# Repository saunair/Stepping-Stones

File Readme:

The code is launched in the master PC by the following commands in different terminals
roslaunch morpheus_skates stepping_stones.launch
rosrun morpheus_skates take_user_input.py
rosrun morpheus_skates shoe_size_input.py

Calibration routine:
roslaunch morpheus_skates calibration_arduino.py

The folder structure is created in a way that all the components are separate from each other
Arduino contains all the object oriented code that runs in each skate
CATKIN workspace contains all the ROS code 
Matlab contains the ROSBAGs, ROSBAG parsing scripts and some simulation files
Mechanical/CAD has all the CAD files of the skates 
Electrical Contains the PCB schematic and layouts used for power distribution and sensing

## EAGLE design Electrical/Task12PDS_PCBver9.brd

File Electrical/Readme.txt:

Schematic and Layout Designs for Power distribution and sensing suite PCB.

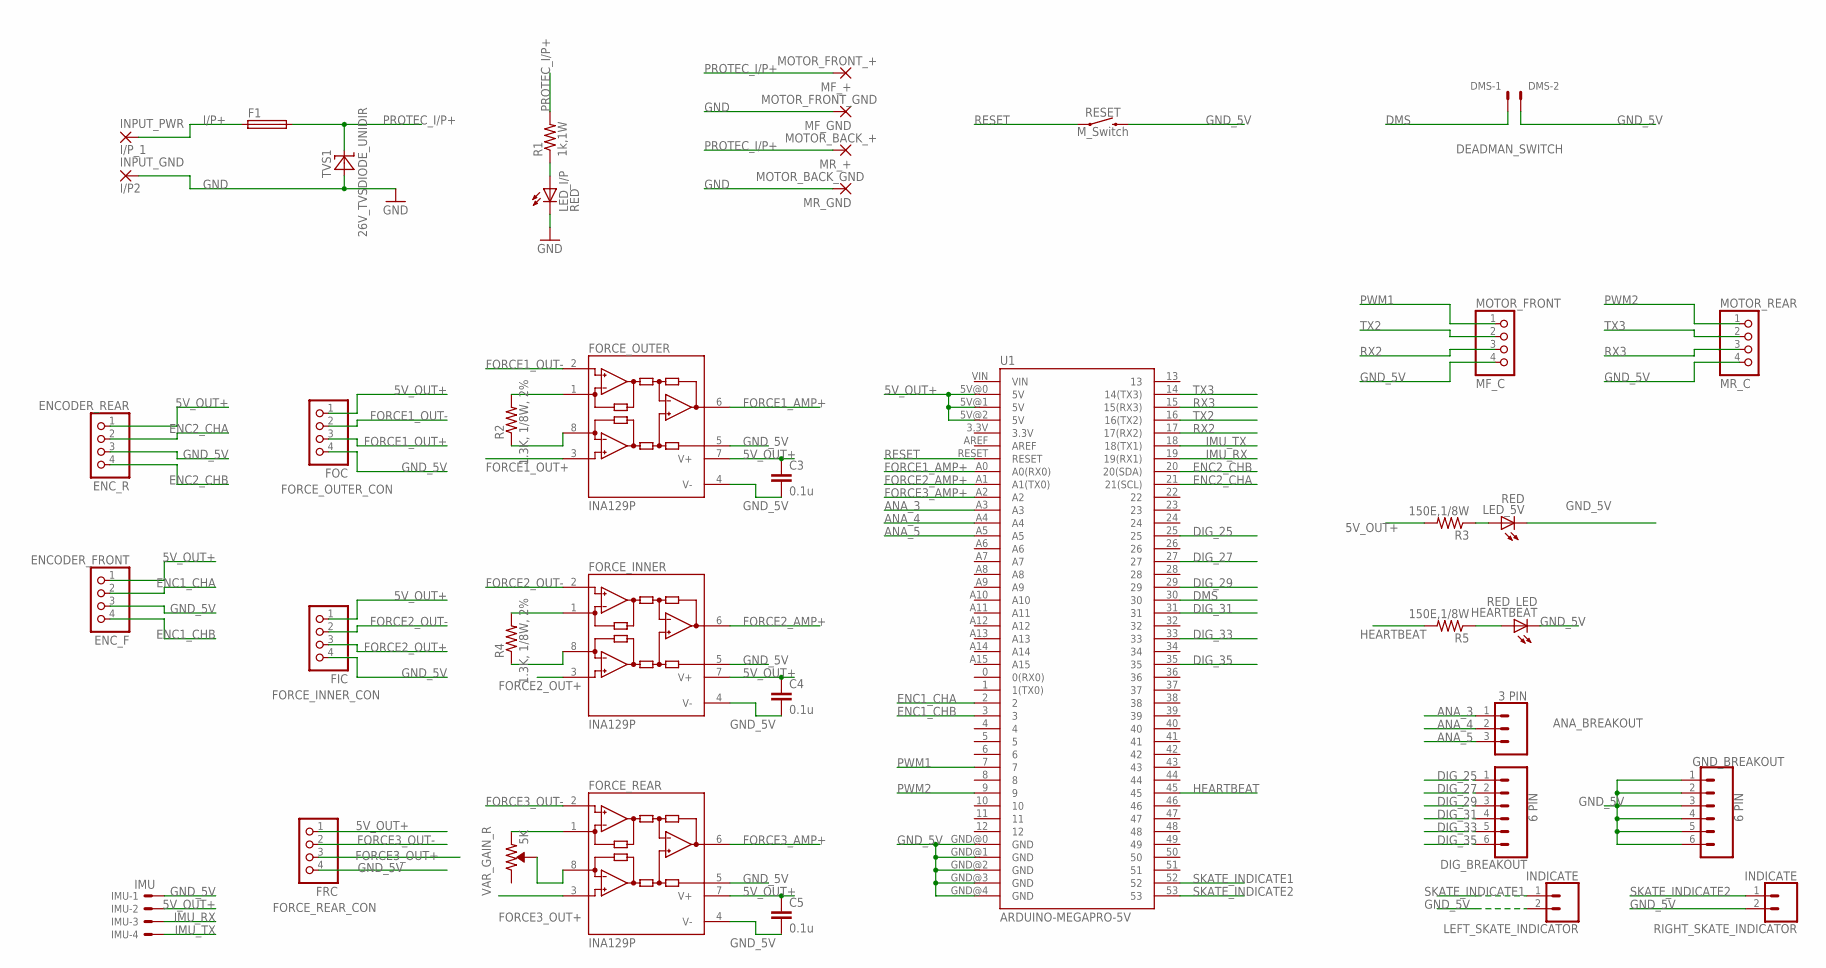
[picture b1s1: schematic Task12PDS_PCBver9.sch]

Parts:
ANA_BREAKOUT: 3 PIN; 1X03
C3, C4, C5: 0.1u; C1206
DIG_BREAKOUT: 6 PIN; 1X06
DMS: DEADMAN_SWITCH; 22-23-2021
ENCODER_FRONT: ENC_F; 1X04/90
ENCODER_REAR: ENC_R; 1X04/90
F1: FASTBLOW_FUSE_10A; TE5
FORCE_INNER: INA129P; DIL08
FORCE_INNER_CON: FIC; 1X04/90
FORCE_OUTER: INA129P; DIL08
FORCE_OUTER_CON: FOC; 1X04/90
FORCE_REAR: INA129P; DIL08
FORCE_REAR_CON: FRC; 1X04/90
GND_BREAKOUT: 6 PIN; 1X06
HEARTBEAT: RED_LED; 1206
IMU: IMU; 22-23-2041
INPUT_GND: I/P2; 3,81/1,1
INPUT_PWR: I/P_1; 3,81/1,1
LED_5V: RED; 1206
LED_I/P: RED; 1206
LEFT_SKATE_INDICATOR: INDICATE; 1X02
MF_+: MOTOR_FRONT_+; 3,81/1,1
MF_GND: MOTOR_FRONT_GND; 3,81/1,1
MOTOR_FRONT: MF_C; 1X04/90
MOTOR_REAR: MR_C; 1X04/90
MR_+: MOTOR_BACK_+; 3,81/1,1
MR_GND: MOTOR_BACK_GND; 3,81/1,1
R1: 1k,1W; M1206
R2, R4: 1.3K, 1/8W, 2%; M1206
R3, R5: 150E,1/8W; M1206
RESET: M_Switch; TACTILE_SWITCH_PTH_6.0MM
RIGHT_SKATE_INDICATOR: INDICATE; 1X02
TVS1: 26V_TVSDIODE_UNIDIR; DO214AC
U1: ARDUINO-MEGAPRO-5V; ARDUINO_MEGA-PRO-5V
VAR_GAIN_R: 5K; TRIMPOT-PTH-3386U

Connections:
5V_OUT+: C3.1, C4.1, C5.1, ENCODER_FRONT.1, ENCODER_REAR.1, FORCE_INNER.7 (V+), FORCE_INNER_CON.1, FORCE_OUTER.7 (V+), FORCE_OUTER_CON.1, FORCE_REAR.7 (V+), FORCE_REAR_CON.1, IMU.2, R3.2, U1.5V@0 (5V), U1.5V@1 (5V), U1.5V@2 (5V)
ANA_3: ANA_BREAKOUT.1, U1.A3
ANA_4: ANA_BREAKOUT.2, U1.A4
ANA_5: ANA_BREAKOUT.3, U1.A5
DIG_25: DIG_BREAKOUT.1, U1.25
DIG_27: DIG_BREAKOUT.2, U1.27
DIG_29: DIG_BREAKOUT.3, U1.29
DIG_31: DIG_BREAKOUT.4, U1.31
DIG_33: DIG_BREAKOUT.5, U1.33
DIG_35: DIG_BREAKOUT.6, U1.35
DMS: DMS.1, U1.30
ENC1_CHA: ENCODER_FRONT.2, U1.2
ENC1_CHB: ENCODER_FRONT.4, U1.3
ENC2_CHA: ENCODER_REAR.2, U1.21 (21(SCL))
ENC2_CHB: ENCODER_REAR.4, U1.20 (20(SDA))
FORCE1_AMP+: FORCE_OUTER.6 (OUT), U1.A0 (A0(RX0))
FORCE1_OUT+: FORCE_OUTER.3 (+IN), FORCE_OUTER_CON.3
FORCE1_OUT-: FORCE_OUTER.2 (-IN), FORCE_OUTER_CON.2
FORCE2_AMP+: FORCE_INNER.6 (OUT), U1.A1 (A1(TX0))
FORCE2_OUT+: FORCE_INNER.3 (+IN), FORCE_INNER_CON.3
FORCE2_OUT-: FORCE_INNER.2 (-IN), FORCE_INNER_CON.2
FORCE3_AMP+: FORCE_REAR.6 (OUT), U1.A2
FORCE3_OUT+: FORCE_REAR.3 (+IN), FORCE_REAR_CON.3
FORCE3_OUT-: FORCE_REAR.2 (-IN), FORCE_REAR_CON.2
GND: INPUT_GND.1, LED_I/P.C, MF_GND.1, MR_GND.1, TVS1.A
GND_5V: C3.2, C4.2, C5.2, DMS.2, ENCODER_FRONT.3, ENCODER_REAR.3, FORCE_INNER.4 (V-), FORCE_INNER.5 (REF), FORCE_INNER_CON.4, FORCE_OUTER.4 (V-), FORCE_OUTER.5 (REF), FORCE_OUTER_CON.4, FORCE_REAR.4 (V-), FORCE_REAR.5 (REF), FORCE_REAR_CON.4, GND_BREAKOUT.1, GND_BREAKOUT.2, GND_BREAKOUT.3, GND_BREAKOUT.4, GND_BREAKOUT.5, GND_BREAKOUT.6, HEARTBEAT.C, IMU.1, LED_5V.C, LEFT_SKATE_INDICATOR.2, MOTOR_FRONT.4, MOTOR_REAR.4, RESET.3 (2), RIGHT_SKATE_INDICATOR.2, U1.GND@0 (GND), U1.GND@1 (GND), U1.GND@2 (GND), U1.GND@3 (GND), U1.GND@4 (GND)
HEARTBEAT: R5.2, U1.45
I/P+: F1.1, INPUT_PWR.1
IMU_RX: IMU.3, U1.19 (19(RX1))
IMU_TX: IMU.4, U1.18 (18(TX1))
unnamed: HEARTBEAT.A, R5.1
unnamed: FORCE_OUTER.1 (RG), R2.2
unnamed: LED_I/P.A, R1.1
unnamed: FORCE_OUTER.8 (RG), R2.1
unnamed: LED_5V.A, R3.1
unnamed: FORCE_INNER.1 (RG), R4.2
unnamed: FORCE_INNER.8 (RG), R4.1
unnamed: FORCE_REAR.1 (RG), VAR_GAIN_R.1 (CCW)
unnamed: FORCE_REAR.8 (RG), VAR_GAIN_R.2 (WIPER)
PROTEC_I/P+: F1.2, MF_+.1, MR_+.1, R1.2, TVS1.C
PWM1: MOTOR_FRONT.1, U1.7
PWM2: MOTOR_REAR.1, U1.9
RESET: RESET.1, U1.RESET
RX2: MOTOR_FRONT.3, U1.17 (17(RX2))
RX3: MOTOR_REAR.3, U1.15 (15(RX3))
SKATE_INDICATE1: LEFT_SKATE_INDICATOR.1, U1.52
SKATE_INDICATE2: RIGHT_SKATE_INDICATOR.1, U1.53
TX2: MOTOR_FRONT.2, U1.16 (16(TX2))
TX3: MOTOR_REAR.2, U1.14 (14(TX3))

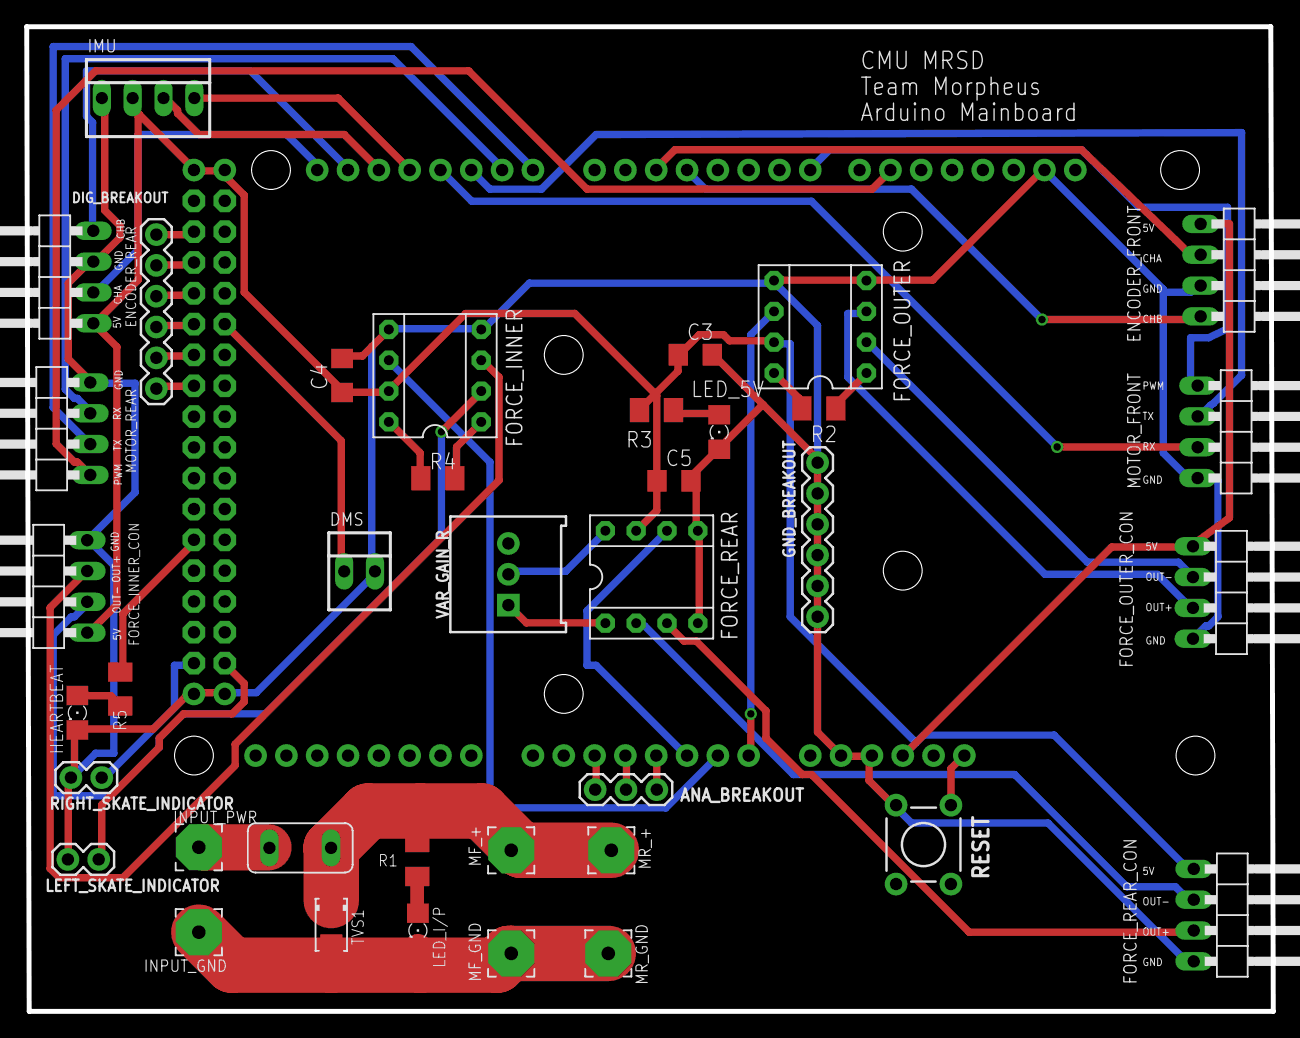
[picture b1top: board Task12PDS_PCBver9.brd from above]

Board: 2 copper layers, 102.7 x 81.2 mm, 40 parts (0 on the bottom side), 49 nets.

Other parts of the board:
DRILEGEND: DRILEGEND

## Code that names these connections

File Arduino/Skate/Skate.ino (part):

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#define FRC_INNER_CH 0
#define FRC_REAR_CH 2

#define ENC1_CHA_PIN 2
#define ENC1_CHB_PIN 3

#define ENC2_CHA_PIN 21
#define ENC2_CHB_PIN 20

#define DEAD_MAN_SW_PIN 30
#define HEARTBEAT_PIN 45

#define CTRL_PERIOD_MS 10.0
#define SAMP_PERIOD_MS 2.0
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
Force forceSensors(FRC_OUTER_CH,FRC_INNER_CH,FRC_REAR_CH);

Drive frontDrive(ENC1_CHA_PIN,ENC1_CHB_PIN,&Serial2); 
Control frontControl(posnGainsFront,velGainsFront,CTRL_PERIOD_MS);

Drive rearDrive(ENC2_CHA_PIN,ENC2_CHB_PIN,&Serial3);
Control rearControl(posnGainsRear,velGainsRear,CTRL_PERIOD_MS);

UM imu;
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  ADMUX  =  bit (REFS0) | (FRC_OUTER_CH & 0x07);    // AVcc and select input port

  //Set Up Front Skate
  attachInterrupt(digitalPinToInterrupt(ENC1_CHA_PIN), doEncoderFrontChA, CHANGE);
  attachInterrupt(digitalPinToInterrupt(ENC1_CHB_PIN), doEncoderFrontChB, CHANGE);
  frontDrive.initializeDrive();
  frontControl.setInvertFlag(leftSkate == true);

  //Set Up Rear Skate
  attachInterrupt(digitalPinToInterrupt(ENC2_CHA_PIN), doEncoderRearChA, CHANGE);
  attachInterrupt(digitalPinToInterrupt(ENC2_CHB_PIN), doEncoderRearChB, CHANGE);
  rearDrive.initializeDrive();
  rearControl.setInvertFlag(leftSkate == true);

  pinMode(DEAD_MAN_SW_PIN, INPUT_PULLUP);
  pinMode(HEARTBEAT_PIN, OUTPUT);

  Serial1.begin(115200);
  Serial1.write(allRequests,21);
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    frontDrive.resetTimeout();
    rearDrive.resetTimeout();

    digitalWrite(HEARTBEAT_PIN,!digitalRead(HEARTBEAT_PIN));
  }
}

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
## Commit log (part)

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2016-11-25 first arduino commit
2016-11-26 "arduino"
2016-11-26 "mechanical"
2016-11-29 "updated arduino codes"
2016-11-29 "new ros codes"
2016-11-30 delayed working code
2016-11-30 at night
2016-11-30 with user input node
2016-11-30 just for arduino
2016-12-01 with new integration code for arduino
2016-12-01 velocity PID working
2016-12-01 Create velocity_control_left
2016-12-01 not working, but compiling arduino
2016-12-07 Add files via upload
    Uploading latest low_level_controller with working position and velocity control. Copy the Servo.h to your local Servo library folder to enable higher speed PWM outputs.
2016-12-07 Create low_level_controller
2016-12-08 with ros integration working and tested
2016-12-08 ros code 7th dec
2016-12-08 with working ros code and skates 11:57pm 7th december
2017-01-26 Updated ROS Arduino code to correct encoder velocity calculation. - Requires testing
2017-01-27 new commit for calibration changes xX
2017-01-27 fixed a bug in the calibration routine
2017-01-30 partially working calibration code
2017-02-01 push for code transition
2017-02-01 brad's
2017-02-01 with the control integration
2017-02-05 removed build
2017-02-05 removed devel
2017-02-05 adding the latest openni launch
2017-02-05 adding the latest openni tracker
2017-02-05 adding the latest rosserial
2017-02-05 Madgwik
2017-02-05 openni_camera
2017-02-05 removing april tage
2017-02-05 Adding serial package
2017-02-05 removing openni-2 files
2017-02-05 removing mrsd packages
2017-02-06 Added serial_motor_commander which accepts a command -100 to +100, maps it to the appropriate pwm command, drives the speed controller, and returns the encoder value.
2017-02-08 heartbeat tetsed
2017-02-08 fixing git
2017-02-08 fixing_git
2017-02-08 fixing_git_rosserial
2017-02-10 removing the useless files
2017-02-12 with faults and kinect centering
2017-02-12 test
2017-02-12 separate faults for skates
2017-02-13 fixed a few offline bugs
2017-02-15 fixed issues
2017-02-15 added files
2017-02-17 Baselined on updated nomenclature PR9_Feb11 code. Starting to split code into libraries.
2017-02-18 untested code
2017-02-18 Created initial object-oriented Arduino software "Skate"
2017-02-18 Added initial keywords.txt for function highlighting, but updates required.
    Added updated mechanical drawing of the aux shaft.
2017-02-19 Now actually deleted install to align
2017-02-19 added mechanical preload code, not tested!
2017-02-20 Started debugging class-based Arduino code, syntax errors and such
2017-02-20 The new class-based code compiles! Ready for minor changes and functional testing/debugging.
2017-02-22 Initial debugging of class-based Arduino code. Position control works on Left Skate. Currently fighting with velocity control - pulsing behavior. Added numerous debugging outputs through ROS. Modifie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
2017-02-24 Completed initial debugging and development of object-based code. Controls still needs work but performs reasonably under load or at speeds of 200 or higher. Replaced moving average filters with trac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
2017-02-24 Changed controller gains to improve performance slightly
2017-02-24 Updated force sensing code after testing. Works for all three sensors.
2017-02-25 partially working calibration
2017-02-25 Started IMU integration coding.
2017-02-25 Updated Arduino code to reintegrate IMU - requires testing. IMU cpp and h moved into Skate folder to resolve compilation issue.
2017-02-25 Corrected IMU request for acceleration
2017-02-26 working normalization
2017-02-27 first compiled imu integrator
2017-02-28 calibration_values
2017-02-28 working calibration with preload
2017-02-28 Arduino code with working, lower rate IMU communication. Also wrote serial sniffer that allows an Arduino to forward and rebroadcast bidirectional serial communication allowing for monitoring from a 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
2017-02-28 Mounts for new PCB location over user's toe-box
2017-02-28 Committed change from this morning that supports more consistent publishing rate.
2017-03-04 trial normalization
2017-03-04 temporary normalization
2017-03-10 Intermediate commit wih 115,200 baud rate to resolve checksum errors. Trying to increase IMU and control loop rates.
2017-03-10 Achieved best balance of rates and capabilities. Control: 100Hz, IMU: 20Hz, Force: 500Hz
2017-03-10 Updated message with new elements including debug entries. Modified launch partially for baud rate.
2017-03-11 Corrected mistake in force reading - thanks Saurabh!
2017-03-11 Added in various minor changes related to skate side, baud, and publish rate.
2017-03-11 Added CAD files for Force Sensor Calibration Rig
2017-03-12 adding rest of the files
2017-03-12 Updates while calibrating. Pounds_display now works.
2017-03-13 Added previous scripts and rosbags. Need new rosbag to continue development.
2017-03-13 Added matlab script development bag. Pounds display message and related changes from yesterday. Cleanup changes from yesterday. Corrections to stepping_stones.py after testing.
2017-03-14 First pass at Matlab script and first rosbag conversion completed.
2017-03-14 With new topics in steping stones and preliminary IMU work
2017-03-15 Added rear terminal holder. Housekeeping of moving files to new spring folder.
2017-03-16 imu for debugging at home
2017-03-17 kou changed the channel numbers
2017-03-19 Created DriveCharacterization sketch to perform open loop motor testing with the VESC-X's. Initial code written, some debugging required for compilation.
2017-03-20 Committing older changes relating to imu integrator and normalization display
2017-03-20 Added VR script files for safe-keeping ahd hopefully to fix catkin_make
2017-03-20 Valid calibration values for all sensors with preload! Update Skate to pull-up digital inputs for skate indicators.
2017-03-20 Compilation errors resolved for the DriveCharacterization sketch. Functional testing still required.
2017-03-20 work for normalization
2017-03-20 fixes to normalization topic
2017-03-21 first bag files
2017-03-21 all bag files for static tests
2017-03-21 COM test data
2017-03-21 Updated DriveCharacterization from first level of functional debugging. Ready to test with VESC-X.
2017-03-21 Renamed scripts folder
2017-03-21 Partial updates to script for two added topics. Initial conversion of two rosbags out of interest.
2017-03-21 Mounts over user's toe-box for new PCB and the IMU
2017-03-22 Rosbag file parsing script
2017-03-22 Wrote script to combine normalized force readings from an experiment. Converted stance tests to mat and csv with script.
2017-03-22 Multiclass SVM for stance determination
2017-03-22 SVM with RBF and model
2017-03-22 Added script for combining com data and .mat combined file.
2017-03-22 Swapped front and rear encoder pin definitions to match new PCB.
2017-03-23 Migrated VESC-X code from DriveCharacterization to Skate. Updated controls code with preliminary feedforward and feedback elements/gains. Benchtop testing required.
2017-03-24 Initial debugging and tuning of VESC control.
2017-03-27 Control updates to handle skate directionality. Successfully tested all 4 motors with this code.
2017-03-27 progress with integrated message
2017-03-27 into test as well
2017-03-28 Updated Skate sketch for new feedback and command naming. Reenabled safety checks. Updated make list to make new essages. Updated subscribers to possible updated messages. Added foot keypoints to mes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
2017-03-28 adding publish rate message
2017-03-29 bug fixes with subscription
2017-03-29 zero point subtraction
2017-03-29 adding changes regarding timeout
2017-03-29 removing calibration enable
2017-03-29 yaml file
2017-03-29 with latest development in aggregated message
2017-03-29 Updates for better safety fault response.
2017-03-30 bag files and message node fix try
2017-03-30 Updates to parseRosbag for command and feedback message changes. Added integrated message but currently results in java memory error. Parsed multiple messages from last rosBag from plotting - noted e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
2017-03-31 Added tf listeners for other Kinect keypoints with print statements to test using stepping stones, success. Silenced repetitive messages for skate faults and timouts. Changed force normalization to u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
2017-04-02 Merged integrated message with stepping stones. Corrected issues in force normalization.
2017-04-02 Closed loop control testing
2017-04-03 Controls State Machine code
    Still in progress, have just laid out a basic skeleton so far; lots to do.
2017-04-03 Controls Skate Machine Skeleton
    Updated, mostly complete; need to fill in controls steps, weighting of the state transitions, discuss conditions for the same
2017-04-04 Open loop motor testing - potential rear left encoder problem and screw interference seized rear right motor in last test.
2017-04-04 Added Matlab ros msg gen stuff including duplication of workspace..sorry
2017-04-04 rosbag for open loop
2017-04-04 Arduino code with freewheeling. Matching rosbags.
2017-04-04 qupdated state machine
2017-04-05 Updated StateMachine works boi
2017-04-05 Ramp and gain updates to Arduino code. Control debug rosbags commited.
2017-04-05 Corrected state machine code
2017-04-05 Arduino code with tuned closed loop PI control. Control loop testing ros bags. Added time to total_message header.
2017-04-05 initial state machine progress
2017-04-07 progress
2017-04-07 state classifier
2017-04-07 Updated DriveCharacterization with revised encoder mapping for new PCB. Updated parseRosbag to parse total message. Completed parsing of first rosbag to .mat and .csv files.
2017-04-07 Added more parsed rosbags. Noticed an issue with the LeftCommand and RightCommand values staying at 0 - need to playback rosbags to determine if issue is in ros or matlab.
2017-04-08 Added conditions for clipping left, right, and total normalized forces. Increased preload threshold warning to 20% to reduce nuisance messages. Needs testing.
2017-04-08 Dummy NN code for velocity mapping
2017-04-08 vr code node
2017-04-09 Updates and bags from tonight's tests
2017-04-09 Parsed rosbags of tests from Saturday night. Finally committing V2 of bearing mount 3D printed part.
2017-04-12 progress with velocity mapper code
2017-04-12 updated with all feature additions
2017-04-12 Updated Arduino code with reduced Ki for tracking loop, new open loop gain, and unloaded Kp and Ki. Also included fix for state changes of brake and freewheeling. Updated stepping stones to remap lef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
2017-04-12 working velocity mapping code
2017-04-12 updated state machine with markov chain
2017-04-13 Initial version of wheel mount - need to correct hole locations and height.
2017-04-14 COM checks and additional code
2017-04-15 updated state machine code
2017-04-15 VR sender updates to node and launch. CL tuning with wheels for Koushik and Brad.
2017-04-15 Updated keystrokes to correct discretization logic.
2017-04-15 Added parsed rosbags from closed loop controls testing.
2017-04-15 state machine updates
2017-04-15 updates in feature vector addition
2017-04-15 State Machine changes
2017-04-15 additions for integration
2017-04-16 INtegrated state machine codes
2017-04-16 latest ROSBAGS model fitting
2017-04-16 Parsed rosbags from 4/15/2017 evening tests.
2017-04-17 rosbags with HDM
2017-04-17 debugs
2017-04-17 updated state machine
2017-04-18 Latest parsed rosbags. Initial comEstimator trial code. Updates to caster replacement CAD and STL files.
2017-04-22 kinect based velocity control
2017-04-22 Updated controller
2017-04-22 Wrote initial e-stop code
2017-04-22 VR update
2017-04-22 Estop stuff
2017-04-22 state machine integration
2017-04-22 Board and Schematic Spring 2017
2017-04-22 Fault Ramp, state machine,VR updates
2017-04-22 cleaning up
2017-04-22 Adding the multiplication for velocities
2017-04-22 Added timeout ramp to Skate code
2017-04-22 changing brakes
2017-04-22 Added one free timeout
2017-04-23 SVE demo test
2017-04-23 vr bug fix
2017-04-23 conflicts resolved
2017-04-23 reseting few lines for publish rate
2017-04-23 final checks
2017-04-23 build problems
2017-04-25 recent vr
2017-04-25 smoothening
2017-04-26 Removing unnecessary comments in the code

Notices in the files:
parts and their libraries:
SparkFun-Boards: Licensing: Creative Commons ShareAlike 4.0 International - https://creativecommons.org/licenses/by-sa/4.0
